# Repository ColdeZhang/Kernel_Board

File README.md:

# Homekit智能家居开发板-核心板（Kernel）

## 0x0 总体概述

- Kernel板主要基于安信可的ESP-12S（后者基于乐鑫ESP8266），为HomeKit智能家居开发准备了一些基础电路。因此更适合没有太多电路基础的新手着手进行Homekit智能家居的开发。相比于ESP-01在保留必须的一部分功能后尽可能的引出了更多的可用IO口（6个），使之可以适应更复杂的项目开发，并且拥有更加稳定的网络连接。项目基于Apple Homekit与ESP8266，并且全部开源。

- 该核心板全部文件托管在：[Github仓库](https://github.com/ColdeZhang/Kernel_Board)

- 该核心板配套的代码教程参见：[ESP8266-Homekit 模板代码](https://github.com/ColdeZhang/Esp8266_Homekit_Template)

- 该核心板配套的扩展版系列目前有：？？、？？、？？、？？

> 从1.0版本开始新增USB-Type-C接口支持供电+烧写程序，无需外接TTL转USB

此页面只显示最新版本开发板的资料，旧版本请移步至具体版本的对应文件夹：[Ver_0_X](https://github.com/ColdeZhang/Kernel_Board/tree/main/Ver_0_X)

## 0x1 特点

### 1.复位功能

- Reset按键可以实行一键重启，免除了切换模式时需要拔插电源重启的麻烦。

### 2.模式切换

- 由于ESP-12S具有两种模式（运行模式与烧写模式），并且需要通过将IO0接地来手动切换。本核心板将此操作使用一个单刀双掷开关（SW1）集成在主板上，可以通过拨动开关一键切换运行模式（Normal）和烧写模式（Flash）。

### 3.重新配对

- 因为配对信息是被写入在ESP-12S的闪存中的，所以通过Reset是无法擦除配对记录来重新配对的。
- 如果需要重新配对需要调用Apple Homekit内置函数来执行闪存内信息的重写，在本核心板配套的[Template代码](https://github.com/ColdeZhang/Esp8266_Homekit_Template)中，该功能已被写在了IO13引脚上。
- 硬件层面通过一个按钮RePair，按下即可重新配对。

### 4.恰到好处的尺寸

- 该核心板拥有恰到好处的尺寸（宽5cm），使其恰好能够放入一个常规开关盒中，十分适合用来制作一些实用的智能家居设备。

## 0x2 使用方法

### 1.运行方法

1. 将右下的开关选择至Normal；
2. 在任意的一个3V3引脚上连接3.3v的直流正极，任意一个GND引脚连接相应的负极即可启动开发板。
3. 在开发中如果需要重启开发板，可以直接按下主控板上的Reset按键执行重启。（该操作不会擦除ESP-12S上内存与闪存的数据）

### 2.烧写程序

1. 将右下的开关选择至Flash，按下Reset按钮执行重启，重启后主控板处于烧写模式；

2. 将USB-Type-C数据线连接至核心板，另一段连接至电脑，即可从电脑烧写程序至开发板了；
3. 烧写完成后需要将开关切换回Normal模式，再按下重启按钮；

## 0x3 外观尺寸

## 0x4 管脚定义

略

## 0x5 原理图

## 0x6 二次开发说明

1. 本项目全部开源，可直接从仓库获得所有工程文件；
2. 项目电路图、pcb以及Gerber文件的生成全部使用[KiCad](https://www.kicad.org)操作（工程文件后缀为pro）；
3. 项目从成本的角度出发，仅使用了单层电路板；
4. 为了便于焊接，在元器件布局以及选型上都并不是电路设计理论上的最优解；
5. 其中ESP-12S可自由替换ESP-12F或同系列芯片；

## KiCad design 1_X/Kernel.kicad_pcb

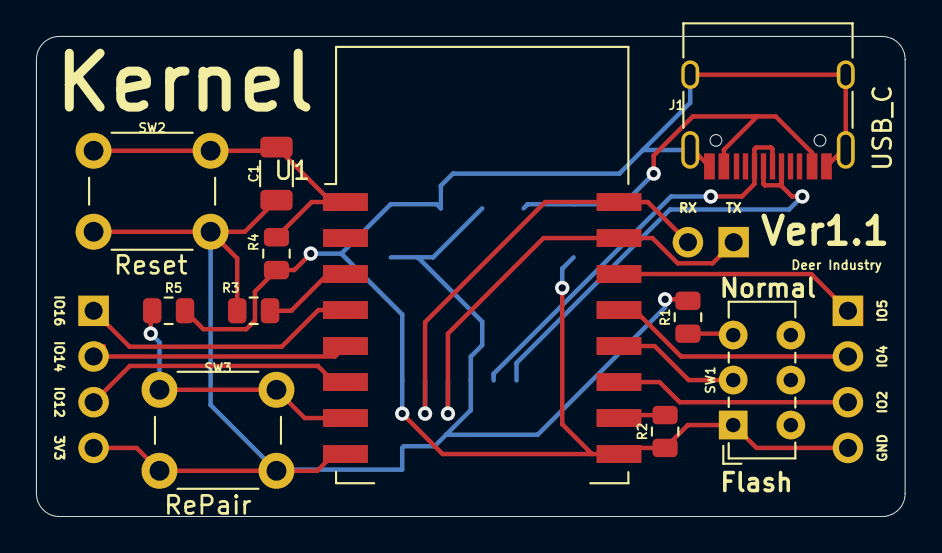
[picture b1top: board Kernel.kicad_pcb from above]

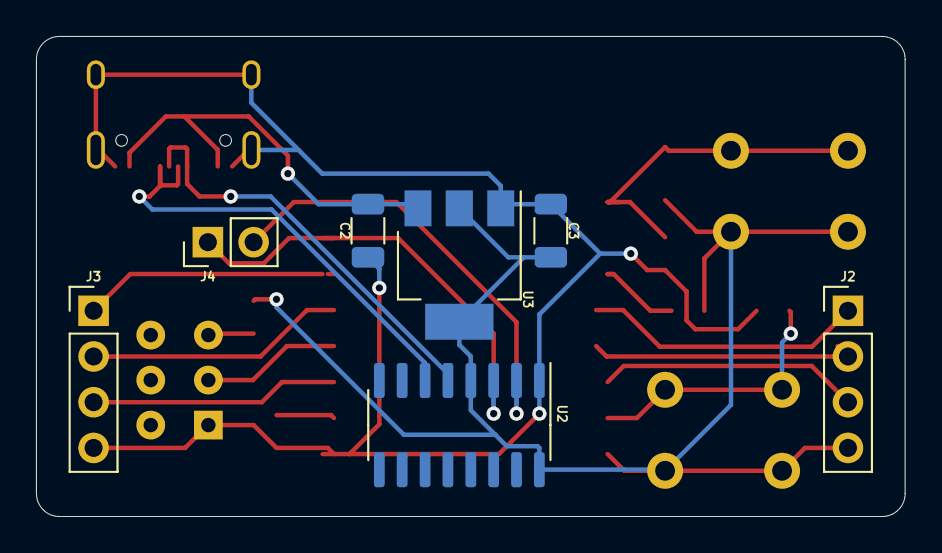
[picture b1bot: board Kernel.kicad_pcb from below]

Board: 2 copper layers, 48.3 x 26.7 mm, 18 parts (7 on the bottom side), 19 nets.

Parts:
C1, C2, C3: 10uF; C_1206_3216Metric
J1: USB_C_Receptacle_USB2.0; USB_C_Receptacle_HRO_TYPE-C-31-M-12
J2: L; PinHeader_1x04_P2.54mm_Vertical
J3: R; PinHeader_1x04_P2.54mm_Vertical
J4: TTL; PinHeader_1x02_P2.54mm_Vertical
R1, R2, R3, R4, R5: 10k; R_0805_2012Metric
SW1: MODE; SW_E-Switch_EG1271_DPDT
SW2: Reset; SW_PUSH_6mm_H4.3mm
SW3: RePair; SW_PUSH_6mm_H4.3mm
U1: ESP-12S-RF_Module; ESP-12E
U2: CH340C; SOIC-16_3.9x9.9mm_P1.27mm
U3: AMS1117-3.3; SOT-223-3_TabPin2

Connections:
+3V3: C1.1, C3.1, J2.4, R1.1, R3.1, SW2.2, SW3.1, U1.8, U2.4, U2.16, U3.2
+5V: C2.1, J1.A4, J1.A9, J1.B4, J1.B9, U3.3
EN: R3.2, U1.3
GND: C2.2, C3.2, J1.A1, J1.A12, J1.B1, J1.B12, J1.S1, J3.4, R2.1, R4.2, R5.1, SW1.1, U1.9, U2.1, U3.1
IO0: SW1.2, U1.12
IO2: J3.3, U1.11
IO4: J3.2, U1.13
IO5: J3.1, U1.14
IO12: J2.3, U1.6
IO13: R5.2, SW3.2, U1.7
IO14: J2.2, U1.5
IO15: R2.2, U1.10
IO16: J2.1, U1.4
unnamed: J1.A6, J1.B6, U2.5
unnamed: J1.A7, J1.B7, U2.6
unnamed: R1.2, SW1.3
RST: C1.2, R4.1, SW2.1, U1.1
RXD: J4.1, U1.15, U2.3
TXD: J4.2, U1.16, U2.2

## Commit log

2021-03-17 update files
2021-03-23 fixed reset
